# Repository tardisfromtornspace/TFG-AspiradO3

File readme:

Proyecto AspiradO3

Nuestro sistema está propuesto para limpiar la troposfera de sustancias químicas nocivas, principalmente el ozono troposférico, pero con unas simples modificaciones también de otros agentes contaminantes como el óxido nitroso, monóxido de carbono y partículas en suspensión, de acuerdo a las ODS 2 (Salud) y 13 (Acción por el clima).
Para ello, según nuestro plan inicial, utilizaríamos un sistema similar a un dirigible o globo aerostático, en el que los sistemas de control y actuación de nuestro dron estarían suspendidos por un globo de un gas ligero, helio o hidrógeno. Esto es para poder llegar a las áreas donde el ozono troposférico se encuentre, y donde un simple filtro a nivel del suelo no pudiera ayudar. El concepto funcionaría de forma similar a una aspiradora, en la que un motor propulsa el aire a través de una serie de filtros que eliminan el gas contaminante, utilizando un filtro de carbón activo, más un par de filtros anti-pájaro y HVAC (no está de más limpiar un poco la atmósfera de polución, ni evitar que nuestro filtro para ozono reaccione con otras sustancias no deseadas), y posiblemente un filtro catabólico selectivo de NOX basado en urea.

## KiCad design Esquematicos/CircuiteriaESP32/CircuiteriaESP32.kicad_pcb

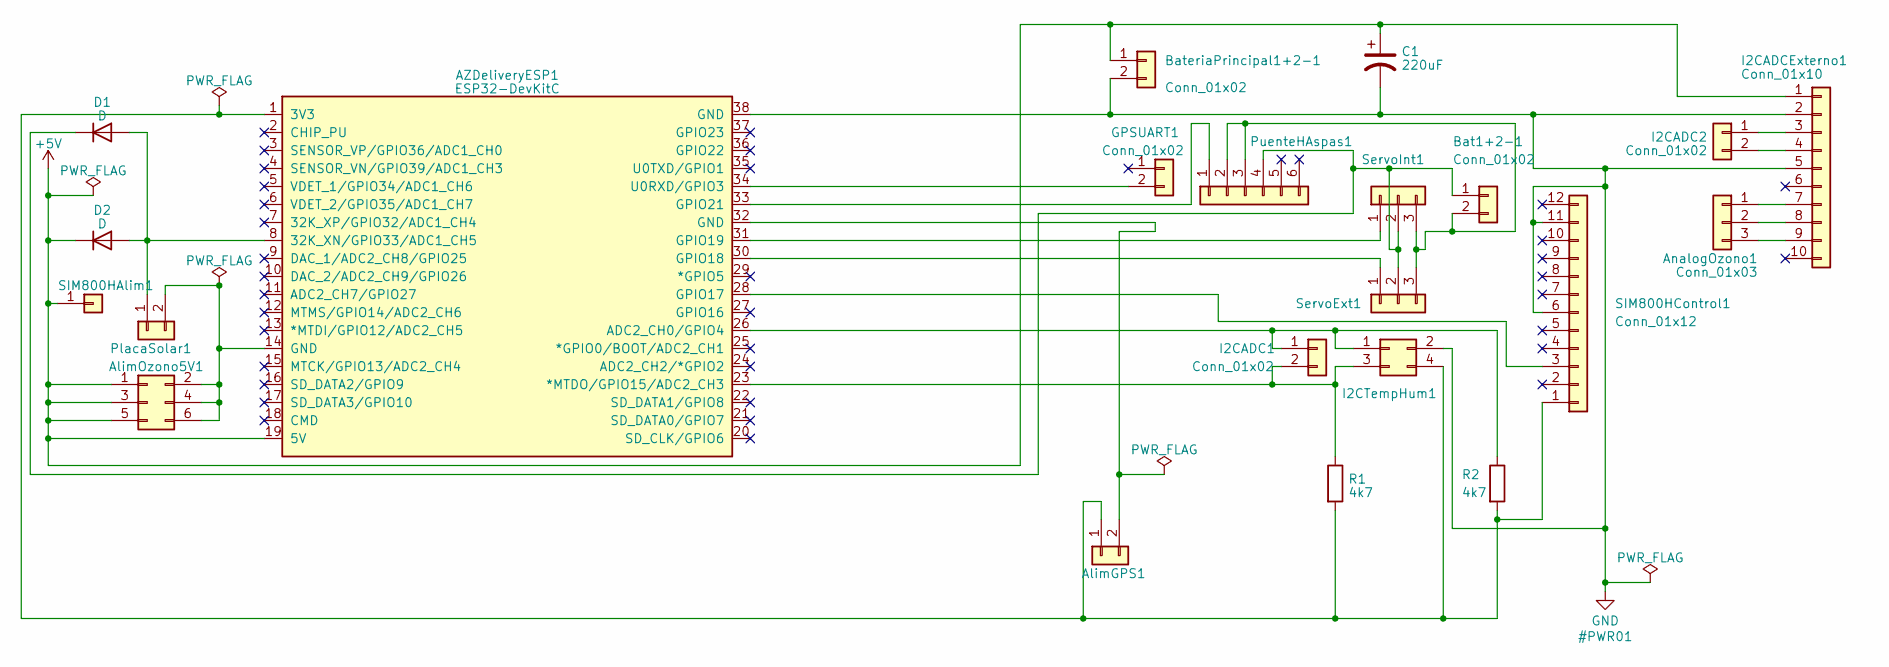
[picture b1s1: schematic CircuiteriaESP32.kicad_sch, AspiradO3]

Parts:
AZDeliveryESP1: ESP32-DevKitC
AlimGPS1: Conn_01x02; PinHeader_1x02_P2.54mm_Vertical
AlimOzono5V1: Conn_02x03_Odd_Even; PinHeader_2x03_P2.54mm_Vertical
AnalogOzono1: Conn_01x03; PinHeader_1x03_P2.54mm_Vertical
Bat1+2-1: Conn_01x02; PinHeader_1x02_P2.54mm_Vertical
BateriaPrincipal1+2-1: Conn_01x02; PinHeader_1x02_P2.54mm_Vertical
C1: 220uF; CP_Radial_D8.0mm_P3.50mm
D1, D2: D; D_T-1_P2.54mm_Vertical_AnodeUp
GPSUART1: Conn_01x02; PinHeader_1x02_P2.54mm_Vertical
I2CADC1, I2CADC2: Conn_01x02; PinHeader_1x02_P2.54mm_Vertical
I2CADCExterno1: Conn_01x10; PinHeader_1x10_P2.54mm_Vertical
I2CTempHum1: Conn_02x02_Odd_Even; PinHeader_2x02_P2.54mm_Vertical
PlacaSolar1: Conn_01x02; PinHeader_1x02_P2.54mm_Vertical
PuenteHAspas1: Conn_01x06; PinHeader_1x06_P2.54mm_Vertical
R1, R2: 4k7; R_Axial_DIN0204_L3.6mm_D1.6mm_P7.62mm_Horizontal
SIM800HAlim1: Conn_01x01; PinHeader_1x01_P2.54mm_Vertical
SIM800HControl1: Conn_01x12; PinHeader_1x12_P2.54mm_Vertical
ServoExt1: Conn_01x03; PinHeader_1x03_P2.54mm_Vertical
ServoInt1: Conn_01x03; PinHeader_1x03_P2.54mm_Vertical

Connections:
+5V: AZDeliveryESP1.19 (5V), AlimOzono5V1.1, AlimOzono5V1.3, AlimOzono5V1.5, BateriaPrincipal1+2-1.1, C1.1, D2.1 (K), I2CADCExterno1.1, SIM800HAlim1.1
GND: AZDeliveryESP1.38 (GND), BateriaPrincipal1+2-1.2, C1.2, I2CADCExterno1.2, I2CADCExterno1.5, I2CTempHum1.2, SIM800HControl1.6, SIM800HControl1.11
unnamed: AZDeliveryESP1.1 (3V3), AlimGPS1.1, I2CTempHum1.4, R1.2, R2.2, SIM800HControl1.1
unnamed: AZDeliveryESP1.8 (32K_XN/GPIO33/ADC1_CH5), D1.2 (A), D2.2 (A), PlacaSolar1.1
unnamed: AZDeliveryESP1.23 (*MTDO/GPIO15/ADC2_CH3), I2CADC1.2, I2CTempHum1.3, R1.1
unnamed: AZDeliveryESP1.26 (ADC2_CH0/GPIO4), I2CADC1.1, I2CTempHum1.1, R2.1
unnamed: AZDeliveryESP1.28 (GPIO17), SIM800HControl1.3
unnamed: AZDeliveryESP1.30 (GPIO18), ServoExt1.1
unnamed: AZDeliveryESP1.31 (GPIO19), ServoInt1.1
unnamed: AZDeliveryESP1.33 (GPIO21), PuenteHAspas1.1
unnamed 10: AZDeliveryESP1.34 (U0RXD/GPIO3), GPSUART1.2; also elsewhere on the board
unnamed: AZDeliveryESP1.32 (GND), AlimGPS1.2
unnamed: AZDeliveryESP1.14 (GND), AlimOzono5V1.2, AlimOzono5V1.4, AlimOzono5V1.6, PlacaSolar1.2
unnamed: AnalogOzono1.1, I2CADCExterno1.7
unnamed: AnalogOzono1.2, I2CADCExterno1.8
unnamed: AnalogOzono1.3, I2CADCExterno1.9
unnamed: Bat1+2-1.1, D1.1 (K), PuenteHAspas1.4, ServoExt1.2, ServoInt1.2
unnamed: Bat1+2-1.2, PuenteHAspas1.2, PuenteHAspas1.3, ServoExt1.3, ServoInt1.3
unnamed: I2CADC2.1, I2CADCExterno1.3
unnamed: I2CADC2.2, I2CADCExterno1.4

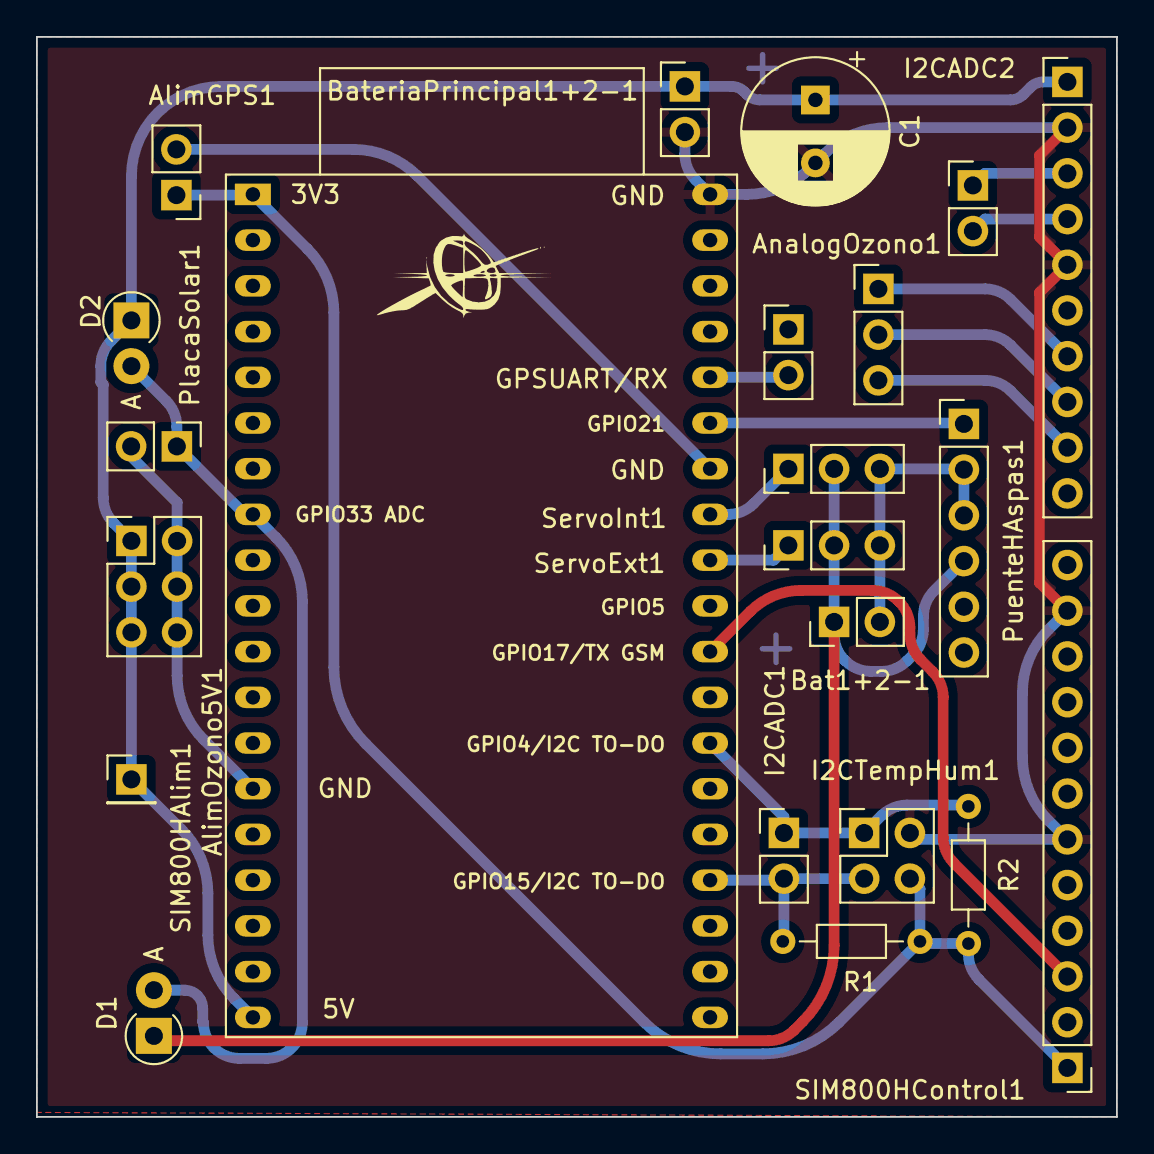
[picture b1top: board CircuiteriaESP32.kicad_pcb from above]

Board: 2 copper layers, 60.0 x 60.0 mm, 22 parts (0 on the bottom side), 20 nets.

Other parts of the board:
GPSUART/RX: Conn_01x02; PinHeader_1x02_P2.54mm_Vertical

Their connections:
unnamed 10: GPSUART/RX.2; also elsewhere on the board

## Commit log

2023-02-08 First commit, using already used code
2023-02-08 Arreglos al código para ver si funcionaría con motores
2023-02-13 Added some ozone sensor thing + suggesting a gps library for later
2023-02-13 Aniadido posible codigo para ozono remesas
2023-02-14 kicad parte 1
2023-02-16 Mejoras en el disenio kicad y más código generado
2023-02-20 código de GPS
2023-02-22 Ajustadas algunas cosas, to-do
2023-02-23 Sensores ozono funcionan
2023-02-28 Actualizado
2023-03-06 Añadido codigo para adafruit i2c
2023-03-08 Prueba i2c nuevo
2023-03-08 Esquematico actualizado
2023-03-08 TFG progreso
2023-03-09 Arreglos para servos y algo de sensores
2023-03-13 actualización con partes del SIM800
2023-03-14 14 marzo 2023
2023-03-15 Actualización motores
2023-03-16 16 de marzo 2023
2023-03-20 Actualización 20 Marzo 2023
2023-03-22 Arreglos
2023-03-23 23 Marzo 2023
2023-03-27 27 marzo 2023, comienzo de desarrollo de un SC, preguntaré más tarde al profesor Norberto
2023-03-29 Arreglos de antes de Semana Santa
2023-04-10 memoria ajustada
2023-04-11 Arreglos sensores 11 abril 2023
2023-04-17 Arreglos 17 abril 2023
2023-04-18 18 abril 2023
2023-04-19 Arreglos 19 abril 2023
2023-04-20 things
2023-04-24 arreglillos
2023-04-26 26 abril 2023
2023-04-27 27 abril 2023
2023-05-01 arreglillos 1 de mayo 2023
2023-05-04 4 de Mayo 2023
2023-05-08 Lunes 8 Mayo 2023
2023-05-09 9 mayo 2023
2023-05-10 10 mayo 2023
2023-05-11 11 de Mayo de 2023
2023-05-15 15 de mayo 2023
2023-05-16 16 mayo 2023
2023-05-17 17 mayo 2023
2023-05-18 18 mayo 2023
2023-05-22 22 de mayo 2023
2023-05-22 22 mayo 2023 parte 2
2023-05-23 una cosa a subir
2023-05-23 Arreglos en limpieza de código
2023-05-23 Arreglos en limpieza de código 2
2023-05-23 otro arreglillo
2023-05-23 23 mayo 2023
2023-05-24 24 mayo 2023
2023-05-25 25 mayo 2023
2023-05-31 31 de mayo 2023
2023-06-01 1 de Junio 2023
2023-06-05 5 junio 2023
2023-06-07 6 y 7 junio 2023
2023-06-13 13 junio 2023
2023-06-16 16 de junio 2023
2023-06-19 19 junio 2023
2023-06-19 19 junio 2023 parte 2
2023-06-21 21 junio 2023
2023-06-23 23 Junio 2023
2023-06-26 26 junio 2023
2023-07-03 3 julio 2023
2023-07-05 5 julio 2023
2023-07-07 7 de julio 2023
2023-07-10 10 julio 2023
2023-07-11 11 de Julio 2023
2023-07-12 12 Julio 2023
2023-07-13 13 julio 2023 parte I
2023-07-13 13 julio 2023 parte II
2023-09-11 11 Septiembre 2023
2023-09-13 13 septiembre 2023
2023-09-14 14 Septiembre 2023, reducción aún mayor de peso
2023-09-19 18 y 19 Septiembre 2023
2023-09-25 25 Septiembre 2023
2023-09-25 25 de Septiembre de 2023 parte 2
2023-09-29 29 Septiembre 2023
2023-10-02 2 de octubre de 2023
2023-10-03 3 octubre 2023
2023-10-05 5 octubre 2023
2023-10-09 9 de Octubre de 2023
2023-10-16 16 octubre 2023
2023-10-23 23 octubre 2023
2023-10-24 24 octubre 2023
2023-10-30 30 octubre 2023
2023-11-06 6 Nov 2023
2023-11-13 13 noviembre 2023
2023-11-14 14 noviembre 2023
2023-11-16 16 noviembre 2023
2023-11-17 17 noviembre 2023
2023-11-20 20 noviembre 2023
2023-11-21 21 noviembre 2023
2023-11-24 24 noviembre 2023
2023-11-27 27 nov 2023
2023-11-28 28 nov 2023
2023-11-29 29 nov 2023 part 1
2023-11-29 29 nov 2023 part 2
2023-12-04 4 diciembre 2023
2023-12-12 11 diciembre 2023
2023-12-18 Arreglos a memoria, 18 Diciembre 2023
2023-12-19 Añadidas imágenes adicionales a la memoria a 19 de diciembre de 2023
2024-01-17 Version 5 de memoria lista
2024-01-17 Memoria versión 6
2024-01-30 Versión 7
2024-01-31 Arreglos extra
2024-02-01 Version 7.2 de la memoria
2024-02-01 Actualización del índice de la versión 7
2024-02-08 Final commit
